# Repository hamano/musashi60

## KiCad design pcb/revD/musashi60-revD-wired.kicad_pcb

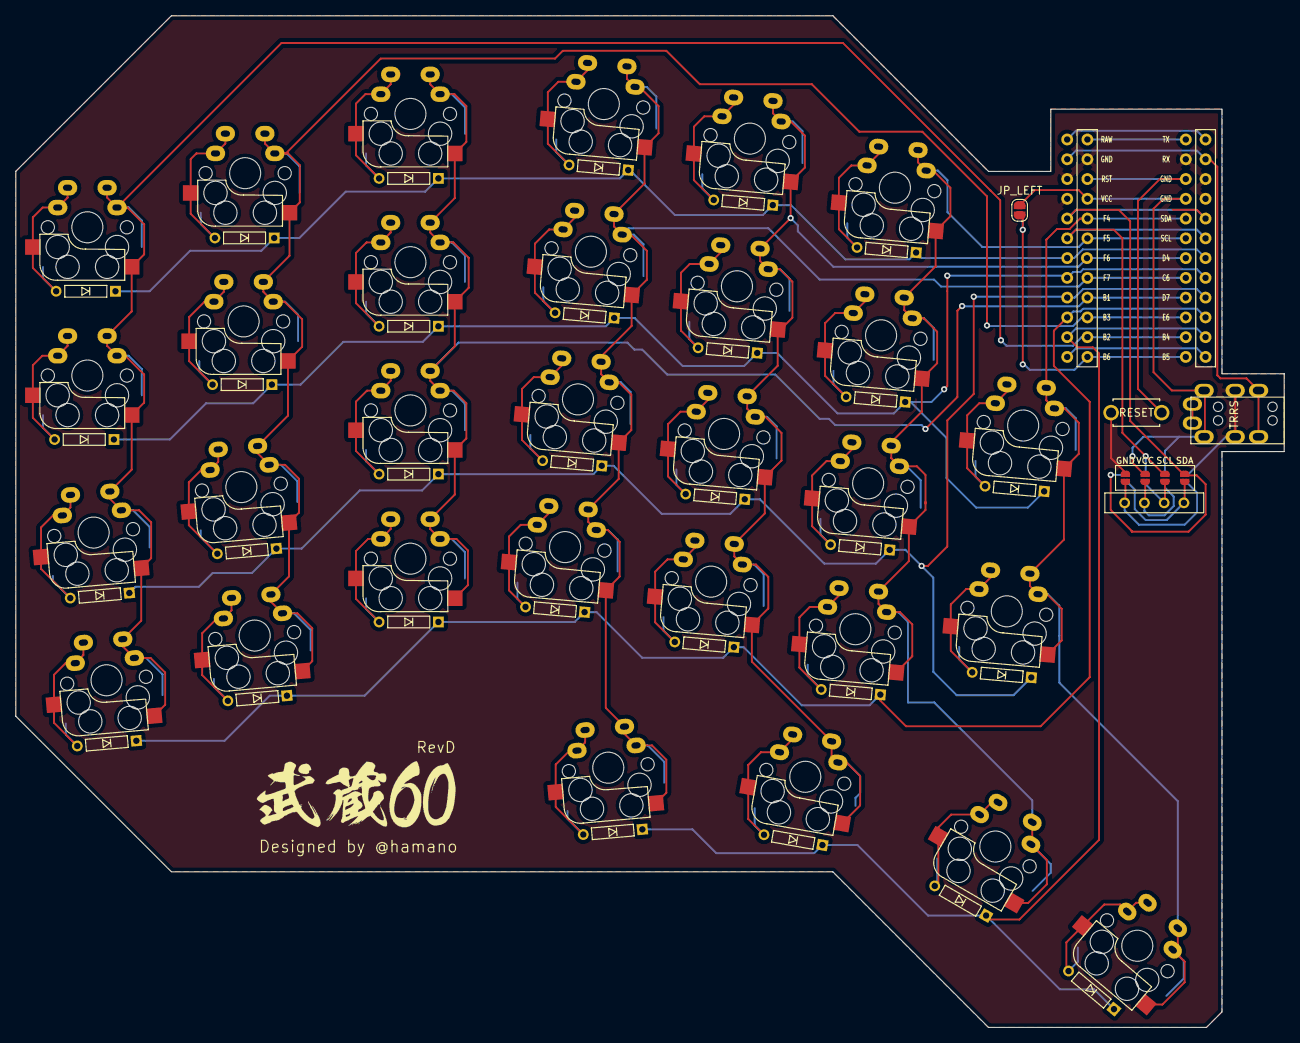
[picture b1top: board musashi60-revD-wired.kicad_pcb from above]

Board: 2 copper layers, 163.0 x 130.0 mm, 67 parts (1 on the bottom side), 53 nets.

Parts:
D_A2, D_A3, D_A5: D; D_TH
D_B1, D_B2, D_B3, D_B4, D_B5: D; D_TH
D_C1, D_C2, D_C3, D_C4, D_C5: D; D_TH
D_D1, D_D2, D_D3, D_D4, D_D5: D; D_TH
D_E1, D_E2, D_E3, D_E4: D; D_TH
D_F1, D_F2, D_F3, D_F4: D; D_TH
D_G1, D_G2, D_G3, D_G4: D; D_TH
J1: MJ-4PP-9
JP_LEFT1: JP_LEFT; SolderJumper
JP_RIGHT1: JP_RIGHT; SolderJumper
OL1: OLED; OLED_Reversible
SW_A2, SW_A3, SW_A5: SW_PUSH; CherryMX_Direct_Hotswap_Reversible
SW_B1, SW_B2, SW_B3, SW_B4, SW_B5: SW_PUSH; CherryMX_Direct_Hotswap_Reversible
SW_C1, SW_C2, SW_C3, SW_C4, SW_C5: SW_PUSH; CherryMX_Direct_Hotswap_Reversible
SW_D1, SW_D2, SW_D3, SW_D4, SW_D5: SW_PUSH; CherryMX_Direct_Hotswap_Reversible
SW_E1, SW_E2, SW_E3, SW_E4: SW_PUSH; CherryMX_Direct_Hotswap_Reversible
SW_F1, SW_F2, SW_F3, SW_F4: SW_PUSH; CherryMX_Direct_Hotswap_Reversible
SW_G1, SW_G2, SW_G3, SW_G4: SW_PUSH; CherryMX_Direct_Hotswap_Reversible
SW_RST1: SW_PUSH; ResetSW
U1: ProMicro_r; ProMicro
U2: OLED_Reversible_Jumper

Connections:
B1: SW_E1.1, SW_E2.1, SW_E3.1, SW_E4.1, U1.16
B2: SW_G1.1, SW_G2.1, SW_G3.1, SW_G4.1, U1.14
B3: SW_F1.1, SW_F2.1, SW_F3.1, SW_F4.1, U1.15
B4: D_A5.1, D_B5.1, D_C5.1, D_D5.1, U1.11
B6: JP_LEFT1.2, JP_RIGHT1.2, U1.13
C6: D_A2.1, D_B2.1, D_C2.1, D_D2.1, D_E2.1, D_F2.1, D_G2.1, U1.8
D0: U1.6, U2.2
D1: U1.5, U2.1
D2: J1.B, U1.2
D4: D_B1.1, D_C1.1, D_D1.1, D_E1.1, D_F1.1, D_G1.1, U1.7
D7: D_A3.1, D_B3.1, D_C3.1, D_D3.1, D_E3.1, D_F3.1, D_G3.1, U1.9
E6: D_B4.1, D_C4.1, D_D4.1, D_E4.1, D_F4.1, D_G4.1, U1.10
F4: SW_A2.1, SW_A3.1, SW_A5.1, U1.20
F5: SW_B1.1, SW_B2.1, SW_B3.1, SW_B4.1, SW_B5.1, U1.19
F6: SW_C1.1, SW_C2.1, SW_C3.1, SW_C4.1, SW_C5.1, U1.18
F7: SW_D1.1, SW_D2.1, SW_D3.1, SW_D4.1, SW_D5.1, U1.17
GND: J1.C, JP_RIGHT1.1, SW_RST1.1, U1.3, U1.4, U1.23, U2.4
unnamed: D_A2.2, SW_A2.2
unnamed: D_A3.2, SW_A3.2
unnamed: D_A5.2, SW_A5.2
unnamed: D_B1.2, SW_B1.2
unnamed: D_B2.2, SW_B2.2
unnamed: D_B3.2, SW_B3.2
unnamed: D_B4.2, SW_B4.2
unnamed: D_B5.2, SW_B5.2
unnamed: D_C1.2, SW_C1.2
unnamed: D_C2.2, SW_C2.2
unnamed: D_C3.2, SW_C3.2
unnamed: D_C4.2, SW_C4.2
unnamed: D_C5.2, SW_C5.2
unnamed: D_D1.2, SW_D1.2
unnamed: D_D2.2, SW_D2.2
unnamed: D_D3.2, SW_D3.2
unnamed: D_D4.2, SW_D4.2
unnamed: D_D5.2, SW_D5.2
unnamed: D_E1.2, SW_E1.2
unnamed: D_E2.2, SW_E2.2
unnamed: D_E3.2, SW_E3.2
unnamed: D_E4.2, SW_E4.2
unnamed: D_F1.2, SW_F1.2
unnamed: D_F2.2, SW_F2.2
unnamed: D_F3.2, SW_F3.2
unnamed: D_F4.2, SW_F4.2
unnamed: D_G1.2, SW_G1.2
unnamed: D_G2.2, SW_G2.2
unnamed: D_G3.2, SW_G3.2
unnamed: D_G4.2, SW_G4.2
unnamed: OL1.1, U2.5
unnamed: OL1.2, U2.6
unnamed: OL1.3, U2.7
unnamed: OL1.4, U2.8
RST: SW_RST1.2, U1.22
VCC: J1.D, JP_LEFT1.1, U1.21, U2.3

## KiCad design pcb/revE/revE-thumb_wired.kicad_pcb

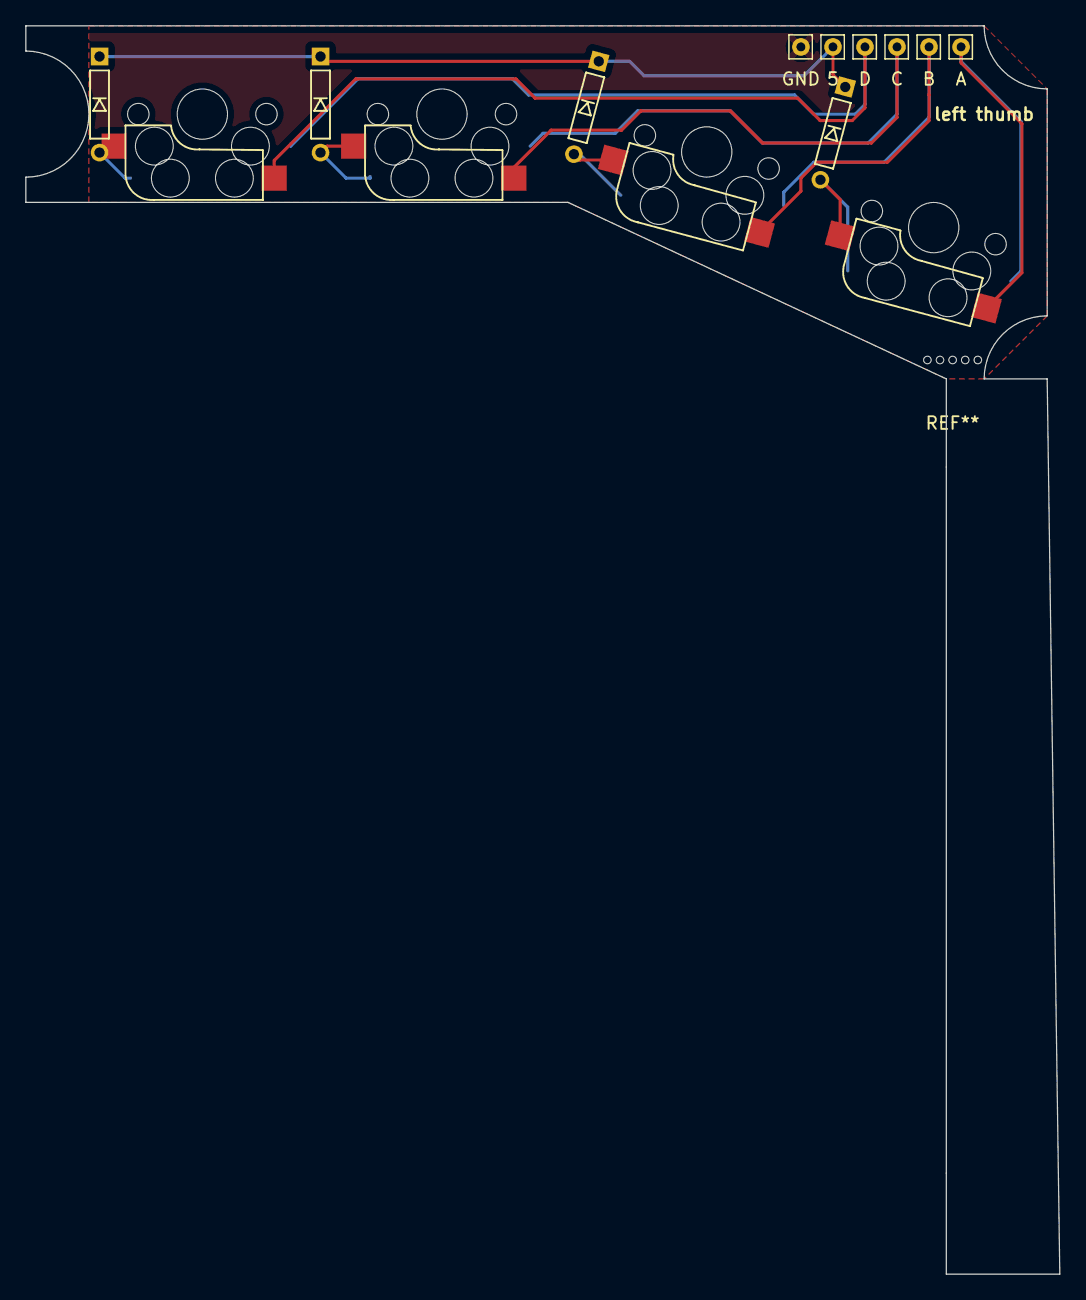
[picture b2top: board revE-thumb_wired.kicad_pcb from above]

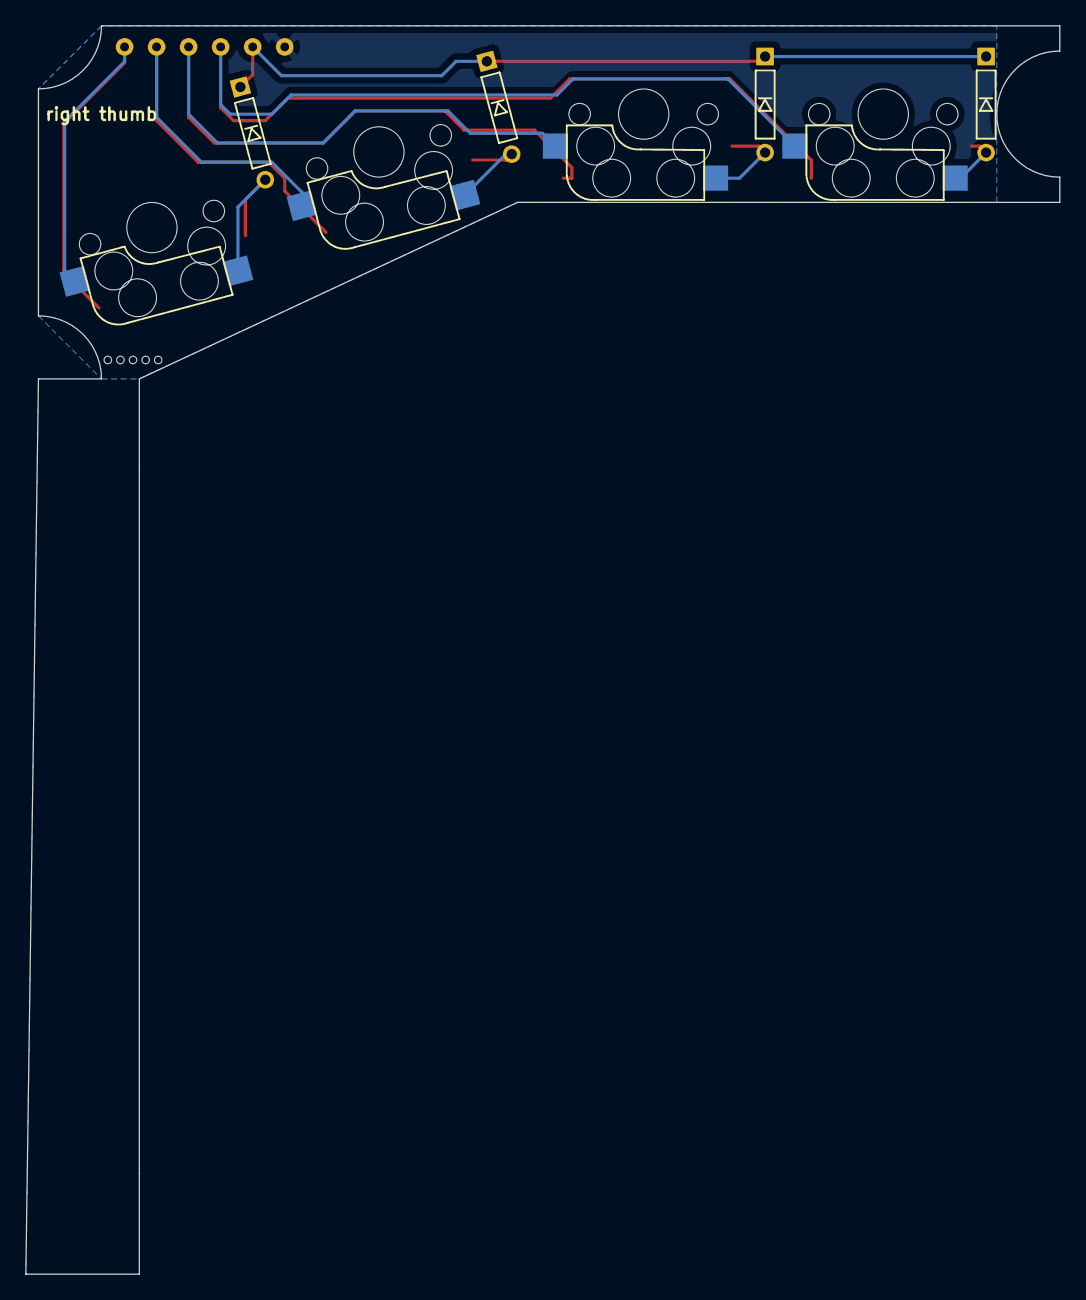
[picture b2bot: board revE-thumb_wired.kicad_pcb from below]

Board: 2 copper layers, 82.0 x 99.0 mm, 14 parts (4 on the bottom side), 9 nets.

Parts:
D_LA5: D_A5; D_TH_Reversible
D_LB5: D_B5; D_TH_Reversible
D_LC5: D_C5; D_TH_Reversible
D_LD5: D; D_TH_Reversible
H_L5: 5; Pin_D0.7mm
H_LA1: A; Pin_D0.7mm
H_LB1: B; Pin_D0.7mm
H_LC1: C; Pin_D0.7mm
H_LD1: D; Pin_D0.7mm
H_LGND1: GND; Pin_D0.7mm
SW_LA5: SW_PUSH-foostan; CherryMX_Hotswap_Reversible
SW_LB5: SW_PUSH-foostan; CherryMX_Hotswap_Reversible
SW_LC5: SW_PUSH-foostan; CherryMX_Hotswap_Reversible
SW_LD5: SW_PUSH-foostan; CherryMX_Hotswap_Reversible

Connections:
unnamed: D_LA5.1, D_LB5.1, D_LC5.1, D_LD5.1, H_L5.1
unnamed: D_LA5.2, SW_LA5.1
unnamed: D_LB5.2, SW_LB5.1
unnamed: D_LC5.2, SW_LC5.1
unnamed: D_LD5.2, SW_LD5.1
unnamed: H_LA1.1, SW_LA5.2
unnamed: H_LB1.1, SW_LB5.2
unnamed: H_LC1.1, SW_LC5.2
unnamed: H_LD1.1, SW_LD5.2
